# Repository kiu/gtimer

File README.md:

# gtimer
gtimer is a programmable controller for the GARDENA [Fully Automatic Flower Box Watering](https://www.gardena.com/int/products/watering/holiday-watering/fully-automatic-flower-box-watering/900916701/) drip system.
Thanks to an ATMEGA microcontroller and a RTC module very flexible watering plans can be achieved. In addition a temperature module influences the timings based on ambient temperature during the course of the day.

gtimer is a drop-in replacement for the GARDENA timer connecting to the original pump of the system.

# Warning
Be aware of what you are doing. You are playing with water and mains voltage in an outdoor environment.
Not only might this kill you, it will hurt the whole time you're dying.

# Nitty-Gritty Details
Checkout the [pics](https://github.com/kiu/gtimer/tree/master/pics) and [hardware](https://github.com/kiu/gtimer/tree/master/hardware) section including BOM, Schematic, PCB layout, firmware, etc.

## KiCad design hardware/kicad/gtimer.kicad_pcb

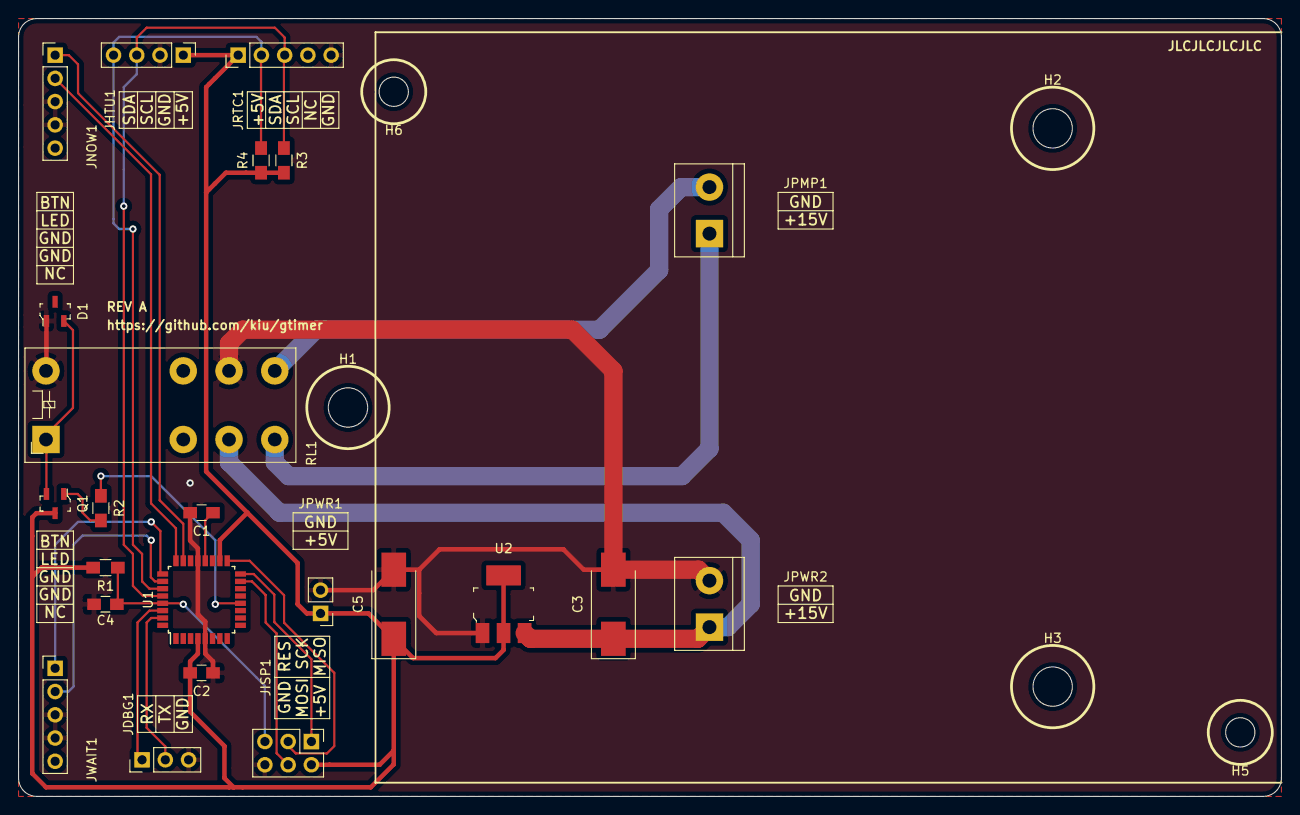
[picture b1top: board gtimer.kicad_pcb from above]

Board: 2 copper layers, 138.0 x 85.0 mm, 28 parts (0 on the bottom side), 21 nets.

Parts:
C1, C2, C4: 100nF; C_0805_HandSoldering
C3, C5: 10uF; CP_Tantalum_Case-D_EIA-7343-31_Hand
D1: BAV99; SOT-23-3
H1, H2, H3: MountingHole; MountingHole_4.3mm_M4
H5, H6: MountingHole; MountingHole_3.2mm_M3
JDBG1: Conn_01x03; Pin_Header_Straight_1x03_Pitch2.54mm
JHTU1: Conn_01x04; Pin_Header_Straight_1x04_Pitch2.54mm
JISP1: Conn_02x03_Odd_Even; Pin_Header_Straight_2x03_Pitch2.54mm
JNOW1: Conn_01x04; Pin_Header_Straight_1x05_Pitch2.54mm
JPMP1: Screw_Terminal_01x02; TerminalBlock_bornier-2_P5.08mm
JPWR1: Conn_01x02; Pin_Header_Straight_1x02_Pitch2.54mm
JPWR2: Screw_Terminal_01x02; TerminalBlock_bornier-2_P5.08mm
JRTC1: Conn_01x05; Pin_Header_Straight_1x05_Pitch2.54mm
JWAIT1: Conn_01x04; Pin_Header_Straight_1x05_Pitch2.54mm
Q1: BC847; SOT-23-3
R1, R3, R4: 10k; R_0805_HandSoldering
R2: 1k; R_0805_HandSoldering
RL1: G2RL-24-DC5; Relay_DPDT_Omron_G2RL-24
U1: ATmega328PB-AU; LQFP-32_7x7mm_Pitch0.8mm
U2: NCP1117ST50T3G; SOT-223

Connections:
+5V: C2.1, C5.1, JHTU1.1, JISP1.2, JPWR1.1, JRTC1.1, Q1.3, R1.1, R3.1, R4.1, U1.4, U1.18, U2.2, U2.4
+15V: C3.1, JPWR2.1, RL1.3, U2.3
BTN_NOW: JNOW1.1, U1.23
BTN_NOW_LED: JNOW1.2, U1.24
BTN_WAIT: JWAIT1.1, U1.25
BTN_WAIT_LED: JWAIT1.2, U1.26
DBG_RX: JDBG1.1, U1.30
DBG_TX: JDBG1.2, U1.31
GND: C1.1, C2.2, C3.2, C4.2, C5.2, D1.1, JDBG1.3, JHTU1.2, JISP1.6, JNOW1.3, JNOW1.4, JPWR1.2, JPWR2.2, JRTC1.5, JWAIT1.3, JWAIT1.4, RL1.6, RL1.8, U1.5, U1.21, U2.1
ISP_MISO: JISP1.1, U1.16
ISP_MOSI: JISP1.4, U1.15
ISP_RES: C4.1, JISP1.5, R1.2, U1.29
ISP_SCK: JISP1.3, U1.17
unnamed: C1.2, U1.20
unnamed: D1.2, Q1.2, RL1.1
unnamed: JPMP1.1, RL1.4
unnamed: JPMP1.2, RL1.5
unnamed: Q1.1, R2.1
RELAY: R2.2, U1.12
TWI_SCL: JHTU1.3, JRTC1.3, R3.2, U1.28
TWI_SDA: JHTU1.4, JRTC1.2, R4.2, U1.27

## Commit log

2021-05-16 Init
2021-05-16 typos
2021-06-05 Initial release
2021-06-05 Drill template
2021-06-05 Adding images
2021-06-05 Bugfix: It can't be 15:00, 18:00 and 21:00 at the same time. doh.
2021-06-05 Additional thumb
2021-06-09 Adjusted timer interval and added RTC sync every 30m Added serial commands Added history of humidity measurements
